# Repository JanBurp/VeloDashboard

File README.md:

# Velo Dashboard

A bicycle computer made for velomobiles.

Walkthrough videos (dutch):
- https://www.youtube.com/watch?v=hqzajXb8Hd0 (inside velomobile)
- https://www.youtube.com/watch?v=B8IcSTC7h3M (test setup)

## Reasons

In the summer of 2022 i bought a second hand [Quest](https://www.velomobiel.nl/quest/) velomobile.
It was in very good shape, had only driven 8000km while only 10 years old, and it fits my budget.

But it was missing blinkers, had a 6V system on board, and two headlights which could be turned on independent from eachother. Which results in my Quest looking cross-eyed :-(
That could be done better.

I also struggled finding the 'perfect' bicycle computer to keep track of at least my current speed, average speed, maximum speed, time, time of the trip, distance, and at least two seperate distance counters.
The most anoying things of these computers are the small screens, the not so ideal combination of functions, button combo's etc. And a GPS one took too long to recognise my location (possibly due to the carbon body).

I took some inspiration found online from other velonauts. Such as:
- [VeloPuter](https://veloputer.wordpress.com/about/)
- [Arduino in VM](https://quest.robbroek.nl/search/label/arduino)
- [Velomobiel Led strip verlichting](https://bickyenzijnfietsen.blogspot.com/2018/10/velomobiel-led-strip-verlichting.html)

## Features

This bicycle computer for a velomibile has these features:

Lighting:
- Drive the normal LED lights that are standard in most velombiles (rear light, brake light, fog light and blinkers if present)
- Drive the (double) head light(s) in several steps (off, dim, normal, beam)
- Drive LED strips on each side of the velomobile. For blinkers (with nice animation!), and normal light for visibility (front, rear and brake lights).

Knobs & Display:
- Big OLED display so i can see it easy.
- All controls are on the steering wheel (with a 3D printed console).
- Knobs for the blinkers, lights and switching through several pages on the display.

Speed & Distance:
- Current speed
- Current average speed
- Current maximum speed
- Distance of current trip
- Total distance of current day
- Distance of previous day
- Average and maximum speed of previous day
- Total distance of the velomobile in total
- Total distance of the velomobile while in my ownership
- At least three different tocal counters wich can be reset independent

Time:
- Current clock time
- Driving time of current trip (excluding stops for traffic lights etc)
- Total time of current trip (including these stops)
- Driving and total time of previous day

Others:
- Current Cadans speed
- Battery status
- Battery saving modes
- Automatic turn off after a set time (to spare battery)
- Option to set the total distance
- Option to set the clock time
- Option to set the wheel circumference
- Optionts to reset all extra counters

# Result

I have a working prototype since december 2022, with several improvements and new featuers since then.

# Manual

## Dashboard

- The yellow buttons are for activating the blinkers. Press and it turns on. Press again to turn off. Press the other and the first one stops and the new one starts. The LED's in front of the dashboard reflects the state of the blinkers.
- The white buttons are for controlling the head and rear lights. And also the lights of the LEDstrips. Press the upper button increases intensity. The lower button decreases intensity. These modes exists: OFF, DIMLIGHT, NORMAL LIGHT, BEAM, FOG.
- The red button on the upper right turns the headlights into BEAM mode while pressed.
- The red button in the middle is not part of the computer: it is it's own circuit and turns of the horn (in my case a Hornitt).
- The black button on the right is for controlling the display on the computer. Pressing cycles to several pages of the display (see below). Long press turns the computer and display into SETUP mode (see below).

## Display modes

Normal pages of the display (cycles through with the blank button):

### Homescreen:
- Speed (big in the center)
- Current distance (topleft)
- Current clock time (topright)
- Average speed (bottomleft)
- Maximun speed (bottomright)
- Cadans / RPM (bottomcenter)
- Icons for headlights and rearligt (middleleft)
- Icons for blinkers and breaklight (topmiddle)
- Icon for battery status (middleright)

### Screen 2 (today):
- Average speed
- Max speed
- Time elapsed while driving (excluding stops)
- Time elapsed from start of driving (including stops)

### Screen 3 (distances):
- Distance of current drive
- Distance of today
- Distance of previous driving day
- Distance of Trip 1

### Screen 3 (totals):
- Total distance of velomobile in my ownershop
- Total distance of velomobile
- Distance of Trip 2
- Distance of Trip 3

## Setup

A long press on the blank button switches to the setup screens. And pressing normal cycles to the setup screens. Long pressing again switches to normal screens. Of the screens there is some help of how to setup the several options.

These are the setup pages:

- Trip - for resetting Trip 1,2 and 3.
- Clock - for setting the time
- Tyre -  for setting the tyre (used for measuring speed and distances). You can select and ERTRO value or in mm.
- Bike - setting the total distance of the bike.

## Others

The computer keeps track of battery status. If the battery is becoming low it will decreases the brightness of the LEDstrips the battery icon on the display starts to blink.

If the battery is very low/almost dead, it will spare itself by turning everything off.

If you forgot to switch the computer off, if will auto power off after three minutes. The last 20 seconds will be shown in the display. If you press a button or start cycling again, the auto-power-off timer will stop.

## Hardware

### Teensy 4.0

The computer is based around a [Teensy 4.0](https://www.pjrc.com/store/teensy40.html). My first attempt was made with a Arduino nano, which is cheaper and uses less power. But i wanted a clock. And the combination of driving LED strips and having an OLED screen was impossible (as far as i know) with te Arduino. The Teensy 4.0 has multiple i2c (OLED) and interrupts. And it also has a build in RTC (Real Time Clock) with power options for a small coin battery to keep the state of the clock. The Teensy has also lots of room for improvements or future additions (SD card storage for example).

### IP67 LEDstrips WS2812B

IP67 means rainproof. And WS2812B means it just has three wires to connect (5V, GND & Data). I have two of them, one for each side of the velomobile. But the computer can also run four of them in case you want four small ones instead of two large ones. I choose the large ones because of easier assembling on my Quest. Downside is it user more power.
Here is a guide for using [WS2812B LEDstrips](https://randomnerdtutorials.com/guide-for-ws2812b-addressable-rgb-led-strip-with-arduino/)

### Power

- For power i choose Lipo batteries of 12.6 Volts. Other batteries are possible.
- [Polo Mini Pushbutton Power Switch](https://www.pololu.com/product/2809) is a on/off switch, whith reverse protection and more.
- Power regulator to 5V. The Teensy has it's own regulator for 5V to 3.3V.

### LED drivers

For driving the front, rear, brake (and maybe blinker) LED's i use [Meanwell LDD Led drivers](https://www.meanwell.com/webapp/product/search.aspx?prod=LDD-L) (LDD-700 for now).

## Schematics

The raw schematics can be found in the [kicad folder](./kicad)

## Software

For developing i used [VScode](https://code.visualstudio.com/) with [PlatformIO](https://platformio.org/). Once setup, i found this much easier for developling compared the Arduino IDE. But thats a software developer speaking ;-)

## 3D print

A STL file for 3D printing the console can be found in the [3D folder](./3d).

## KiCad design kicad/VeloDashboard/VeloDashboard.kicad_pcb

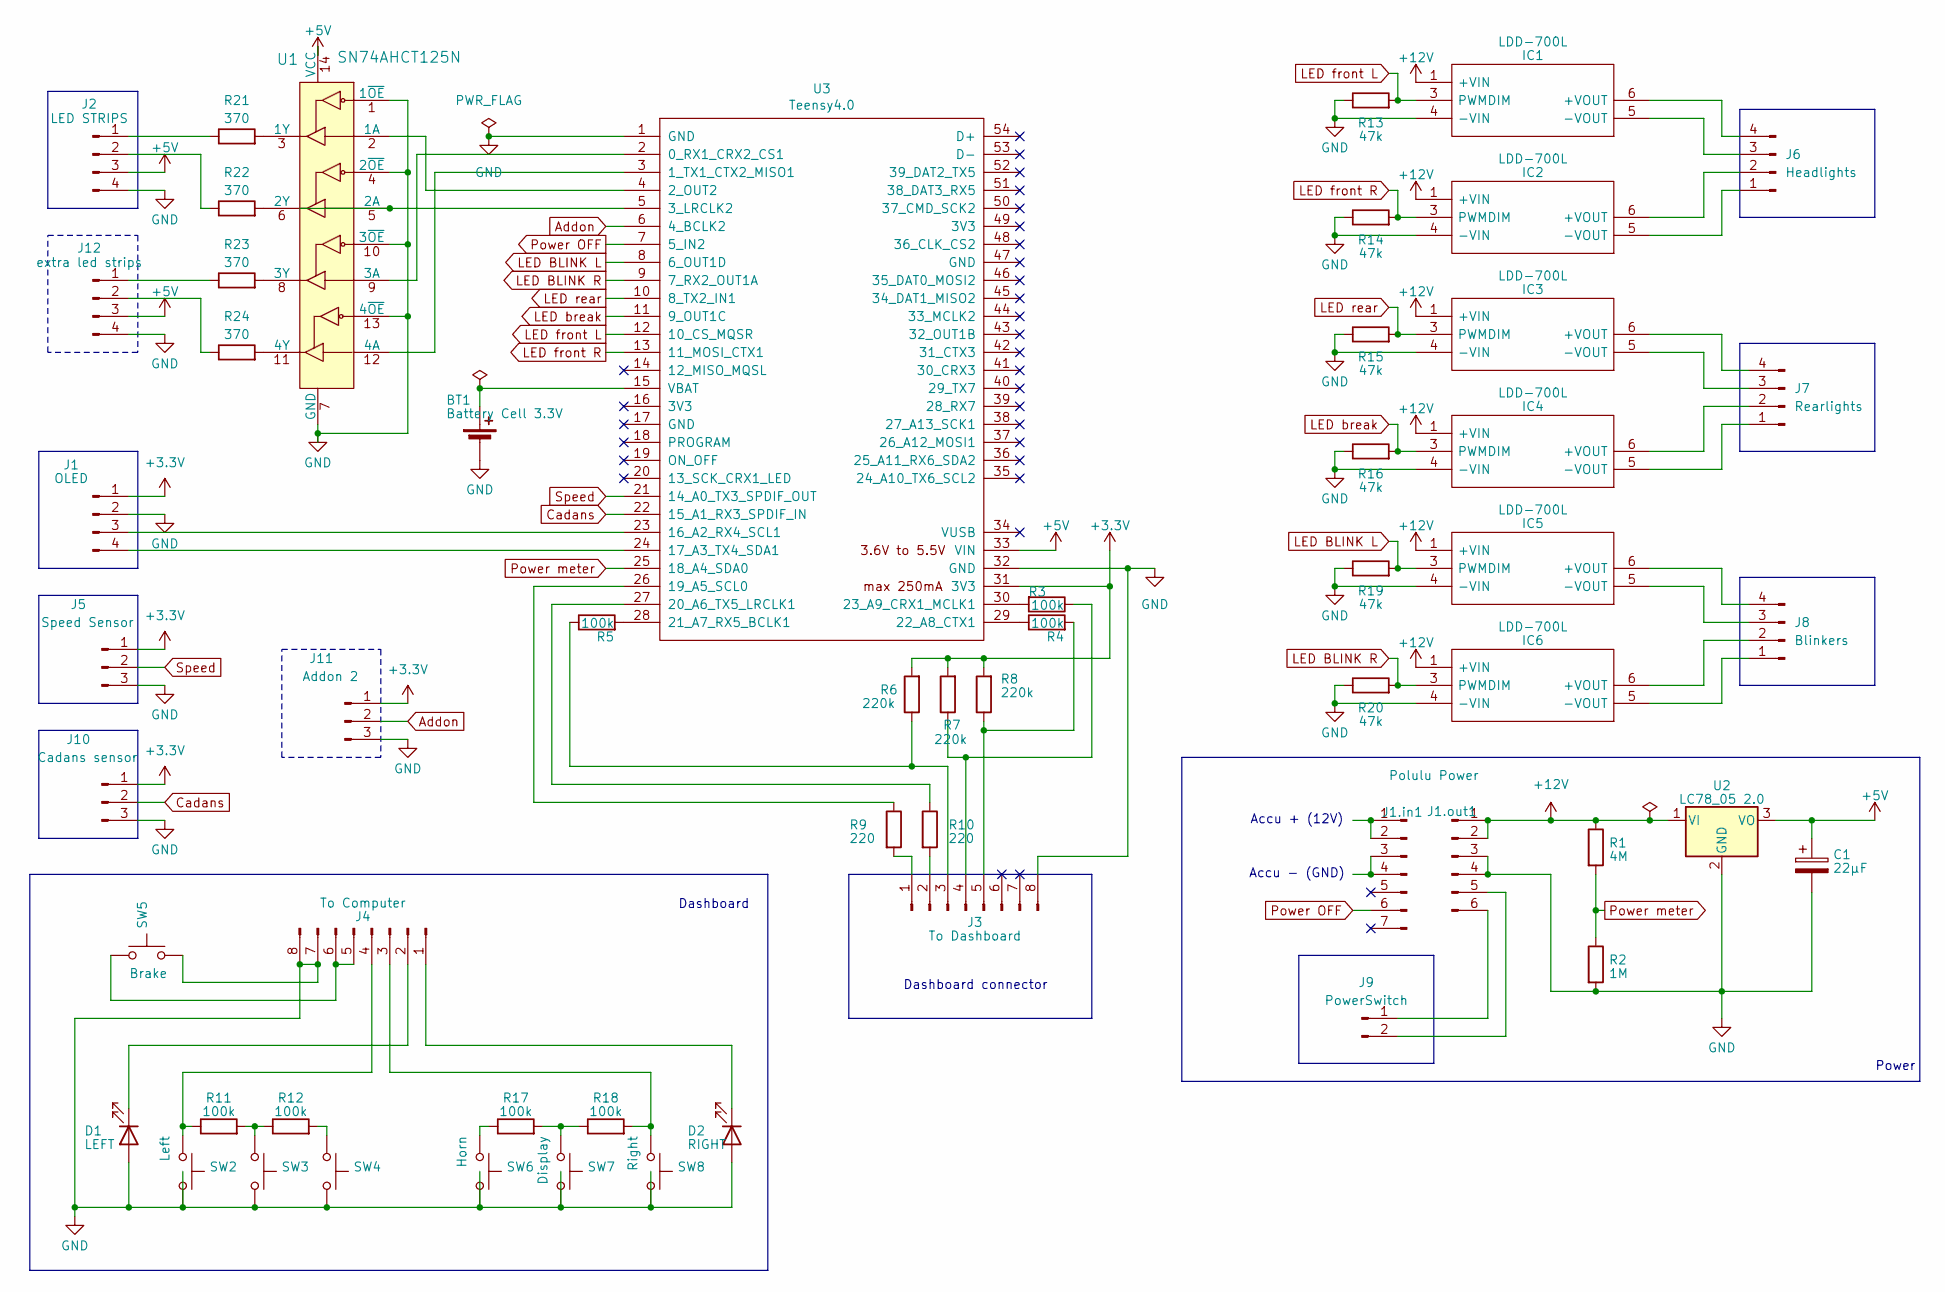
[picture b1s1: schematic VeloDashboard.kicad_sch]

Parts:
BT1: Battery Cell 3.3V; Battery_Panasonic_CR2032-HFN_Horizontal_CircularHoles
C1: 22µF; CP_Radial_D10.0mm_P7.50mm
D1: LEFT; LED_D5.0mm_Clear
D2: RIGHT; LED_D5.0mm_Clear
IC1, IC2, IC3, IC4, IC5, IC6: LDD-700L; LDD-XXXL; Mouser Part Number 709-LDD-700L
J1: OLED; PinHeader_1x04_P2.54mm_Horizontal
J1.in1: PinHeader_1x07_P2.54mm_Horizontal
J1.out1: Polulu Power; PinHeader_1x06_P2.54mm_Horizontal
J2: LED STRIPS; PinHeader_1x04_P2.54mm_Horizontal
J3: To Dashboard; PinHeader_1x08_P2.54mm_Horizontal
J4: To Computer; PinHeader_1x08_P2.54mm_Horizontal
J5: Speed Sensor; PinHeader_1x03_P2.54mm_Horizontal
J6: Headlights; PinHeader_1x04_P2.54mm_Horizontal
J7: Rearlights; PinHeader_1x04_P2.54mm_Horizontal
J8: Blinkers; PinHeader_1x04_P2.54mm_Horizontal
J9: PowerSwitch; PinHeader_1x02_P2.54mm_Horizontal
J10: Cadans sensor; PinHeader_1x03_P2.54mm_Horizontal
J11: Addon 2; PinHeader_1x03_P2.54mm_Horizontal
J12: extra led strips; PinHeader_1x04_P2.54mm_Horizontal
R1: 4M; R_Axial_DIN0207_L6.3mm_D2.5mm_P10.16mm_Horizontal
R2: 1M; R_Axial_DIN0207_L6.3mm_D2.5mm_P10.16mm_Horizontal
R3, R4, R5, R11, R12, R17, R18: 100k; R_Axial_DIN0207_L6.3mm_D2.5mm_P10.16mm_Horizontal
R6, R7, R8: 220k; R_Axial_DIN0207_L6.3mm_D2.5mm_P10.16mm_Horizontal
R9, R10: 220; R_Axial_DIN0207_L6.3mm_D2.5mm_P10.16mm_Horizontal
R13, R14, R15, R16, R19, R20: 47k; R_Axial_DIN0207_L6.3mm_D2.5mm_P10.16mm_Horizontal
R21, R22, R23, R24: 370; R_Axial_DIN0207_L6.3mm_D2.5mm_P10.16mm_Horizontal
SW2: Left; SW_PUSH-12mm
SW3: Down (lights); SW_PUSH-12mm
SW4: Up (lights); SW_PUSH-12mm
SW5: Brake; SW_PUSH-12mm
SW6: Horn; SW_PUSH-12mm
SW7: Display; SW_PUSH-12mm
SW8: Right; SW_PUSH-12mm
U1: SN74AHCT125N; DIP-14_W7.62mm_Socket_LongPads; MPN SN74AHCT125N; Digi-Key_PN 296-4655-5-ND
U2: LC78_05 2.0; TO-220-3_Vertical
U3: Teensy4.0; Teensy40_SMT

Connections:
+3.3V: J1.1, J5.1, J10.1, J11.1, R6.2, R7.2, R8.2, U3.31 (3V3)
+5V: C1.1, J2.3, J12.3, U1.14 (VCC), U2.3 (VO), U3.33 (VIN)
+12V: IC1.1 (+VIN), IC2.1 (+VIN), IC3.1 (+VIN), IC4.1 (+VIN), IC5.1 (+VIN), IC6.1 (+VIN), J1.out1.1, J1.out1.2, R1.1, U2.1 (VI)
Addon: J11.2, U3.6 (4_BCLK2)
Cadans: J10.2, U3.22 (15_A1_RX3_SPDIF_IN)
GND: BT1.2 (-), C1.2, D1.2 (A), D2.2 (A), IC1.4 (-VIN), IC2.4 (-VIN), IC3.4 (-VIN), IC4.4 (-VIN), IC5.4 (-VIN), IC6.4 (-VIN), J1.2, J1.out1.3, J1.out1.4, J2.4, J3.8, J4.7, J4.8, J5.3, J10.3, J11.3, J12.4, R2.2, R13.1, R14.1, R15.1, R16.1, R19.1, R20.1, SW2.2, SW3.2, SW4.2, SW5.2, SW6.2, SW7.2, SW8.2, U1.1 (1~OE), U1.4 (2~OE), U1.7 (GND), U1.10 (3~OE), U1.13 (4~OE), U2.2 (GND), U3.1 (GND), U3.32 (GND)
LED BLINK L: IC5.3 (PWMDIM), R19.2, U3.8 (6_OUT1D)
LED BLINK R: IC6.3 (PWMDIM), R20.2, U3.9 (7_RX2_OUT1A)
LED break: IC4.3 (PWMDIM), R16.2, U3.11 (9_OUT1C)
LED front L: IC1.3 (PWMDIM), R13.2, U3.12 (10_CS_MQSR)
LED front R: IC2.3 (PWMDIM), R14.2, U3.13 (11_MOSI_CTX1)
LED rear: IC3.3 (PWMDIM), R15.2, U3.10 (8_TX2_IN1)
unnamed: BT1.1 (+), U3.15 (VBAT)
unnamed: D1.1 (K), J4.2
unnamed: D2.1 (K), J4.1
unnamed: IC1.6 (+VOUT), J6.4
unnamed: IC1.5 (-VOUT), J6.3
unnamed: IC2.6 (+VOUT), J6.2
unnamed: IC2.5 (-VOUT), J6.1
unnamed: IC3.6 (+VOUT), J7.4
unnamed: IC3.5 (-VOUT), J7.3
unnamed: IC4.6 (+VOUT), J7.2
unnamed: IC4.5 (-VOUT), J7.1
unnamed: IC5.6 (+VOUT), J8.4
unnamed: IC5.5 (-VOUT), J8.3
unnamed: IC6.6 (+VOUT), J8.2
unnamed: IC6.5 (-VOUT), J8.1
unnamed: J1.3, U3.23 (16_A2_RX4_SCL1)
unnamed: J1.4, U3.24 (17_A3_TX4_SDA1)
unnamed: J1.in1.1, J1.in1.2
unnamed: J1.in1.3, J1.in1.4
unnamed: J1.out1.5, J9.2
unnamed: J1.out1.6, J9.1
unnamed: J2.1, R21.1
unnamed: J2.2, R22.1
unnamed: J3.1, R9.2
unnamed: J3.2, R10.2
unnamed: J3.3, R5.1, R6.1
unnamed: J3.4, R3.1, R7.1
unnamed: J3.5, R4.2, R8.1
unnamed: J4.3, R18.2, SW8.1
unnamed: J4.4, R11.1, SW2.1
unnamed: J4.5, J4.6, SW5.1
unnamed: J12.1, R23.1
unnamed: J12.2, R24.1
unnamed: R11.2, R12.1, SW3.1
unnamed: R12.2, SW4.1
unnamed: R17.1, SW6.1
unnamed: R17.2, R18.1, SW7.1
unnamed: U1.2 (1A), U3.4 (2_OUT2)
unnamed: R21.2, U1.3 (1Y)
unnamed: U1.5 (2A), U3.5 (3_LRCLK2)
unnamed: R22.2, U1.6 (2Y)
unnamed: U1.9 (3A), U3.2 (0_RX1_CRX2_CS1)
unnamed: R23.2, U1.8 (3Y)
unnamed: U1.12 (4A), U3.3 (1_TX1_CTX2_MISO1)
unnamed: R24.2, U1.11 (4Y)
unnamed: R9.1, U3.26 (19_A5_SCL0)
unnamed: R10.1, U3.27 (20_A6_TX5_LRCLK1)
unnamed: R5.2, U3.28 (21_A7_RX5_BCLK1)
unnamed: R4.1, U3.29 (22_A8_CTX1)
unnamed: R3.2, U3.30 (23_A9_CRX1_MCLK1)
Power OFF: J1.in1.6, U3.7 (5_IN2)
Power meter: R1.2, R2.1, U3.25 (18_A4_SDA0)
Speed: J5.2, U3.21 (14_A0_TX3_SPDIF_OUT)

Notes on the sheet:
Accu - (GND)
Dashboard
Power
Accu + (12V)
Dashboard connector

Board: 2 copper layers, 58 parts (0 on the bottom side), 65 nets, no tracks yet.

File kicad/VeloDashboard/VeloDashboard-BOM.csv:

"Reference","Value","Datasheet","Footprint","Qty","DNP"
"BT1","Battery Cell 3.3V","~","Battery:Battery_Panasonic_CR2032-HFN_Horizontal_CircularHoles","1",""
"C1","22µF","~","Capacitor_THT:CP_Radial_D10.0mm_P7.50mm","1",""
"D1","LEFT","~","LED_THT:LED_D5.0mm_Clear","1",""
"D2","RIGHT","~","LED_THT:LED_D5.0mm_Clear","1",""
"IC1,IC2,IC3,IC4,IC5,IC6","LDD-700L","https://datasheet.datasheetarchive.com/originals/distributor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","LDD:LDD-XXXL","6",""
"J1","OLED","~","Connector_PinHeader_2.54mm:PinHeader_1x04_P2.54mm_Horizontal","1",""
"J1.in1","~","~","Connector_PinHeader_2.54mm:PinHeader_1x07_P2.54mm_Horizontal","1",""
"J1.out1","Polulu Power","~","Connector_PinHeader_2.54mm:PinHeader_1x06_P2.54mm_Horizontal","1",""
"J2","LED STRIPS","~","Connector_PinHeader_2.54mm:PinHeader_1x04_P2.54mm_Horizontal","1",""
"J3","To Dashboard","~","Connector_PinHeader_2.54mm:PinHeader_1x08_P2.54mm_Horizontal","1",""
"J4","To Computer","~","Connector_PinHeader_2.54mm:PinHeader_1x08_P2.54mm_Horizontal","1",""
"J5","Speed Sensor","~","Connector_PinHeader_2.54mm:PinHeader_1x03_P2.54mm_Horizontal","1",""
"J6","Headlights","~","Connector_PinHeader_2.54mm:PinHeader_1x04_P2.54mm_Horizontal","1",""
"J7","Rearlights","~","Connector_PinHeader_2.54mm:PinHeader_1x04_P2.54mm_Horizontal","1",""
"J8","Blinkers","~","Connector_PinHeader_2.54mm:PinHeader_1x04_P2.54mm_Horizontal","1",""
"J9","PowerSwitch","~","Connector_PinHeader_2.54mm:PinHeader_1x02_P2.54mm_Horizontal","1",""
"J10","Addon 1","~","Connector_PinHeader_2.54mm:PinHeader_1x03_P2.54mm_Horizontal","1",""
"J11","Addon 2","~","Connector_PinHeader_2.54mm:PinHeader_1x03_P2.54mm_Horizontal","1",""
"J12","extra led strips","~","Connector_PinHeader_2.54mm:PinHeader_1x04_P2.54mm_Horizontal","1",""
"R1","4M","~","Resistor_THT:R_Axial_DIN0207_L6.3mm_D2.5mm_P10.16mm_Horizontal","1",""
"R2","1M","~","Resistor_THT:R_Axial_DIN0207_L6.3mm_D2.5mm_P10.16mm_Horizontal","1",""
"R3,R4,R5,R11,R12,R17,R18","100k","~","Resistor_THT:R_Axial_DIN0207_L6.3mm_D2.5mm_P10.16mm_Horizontal","7",""
"R6,R7,R8","220k","~","Resistor_THT:R_Axial_DIN0207_L6.3mm_D2.5mm_P10.16mm_Horizontal","3",""
"R9,R10","220","~","Resistor_THT:R_Axial_DIN0207_L6.3mm_D2.5mm_P10.16mm_Horizontal","2",""
"R13,R14,R15,R16,R19,R20","47k","~","Resistor_THT:R_Axial_DIN0207_L6.3mm_D2.5mm_P10.16mm_Horizontal","6",""
"R21,R22,R23,R24","370","~","Resistor_THT:R_Axial_DIN0207_L6.3mm_D2.5mm_P10.16mm_Horizontal","4",""
"SW2","Left","~","Button_Switch_THT:SW_PUSH-12mm","1",""
"SW3","Down (lights)","~","Button_Switch_THT:SW_PUSH-12mm","1",""
"SW4","Up (lights)","~","Button_Switch_THT:SW_PUSH-12mm","1",""
"SW5","Brake","~","Button_Switch_THT:SW_PUSH-12mm","1",""
"SW6","Horn","~","Button_Switch_THT:SW_PUSH-12mm","1",""
"SW7","Display","~","Button_Switch_THT:SW_PUSH-12mm","1",""
"SW8","Right","~","Button_Switch_THT:SW_PUSH-12mm","1",""
"U1","SN74AHCT125N","http://www.ti.com/general/docs/suppproductinfo.tsp?distId=10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","Package_DIP:DIP-14_W7.62mm_Socket_LongPads","1",""
"U2","LC78_05 2.0","https://www.onsemi.cn/PowerSolutions/document/MC7800-D.PDF","Package_TO_SOT_THT:TO-220-3_Vertical","1",""
"U3","Teensy4.0","","Teensy:Teensy40_SMT","1",""

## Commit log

2022-08-14 Working with simple LED’s
2022-08-14 Buzzer & Timings
2022-08-15 LEDstrips added
2022-08-16 Startup Animation
2022-08-16 Time adjustments
2022-08-20 Speed sensor & Display
2022-08-27 Speed stuff
2022-08-27 PlatformIO
2022-08-27 Speed Display
2022-08-27 Working on Teensy
2022-08-27 Refacturing Speed & Display
2022-08-27 LED strips working
2022-08-27 Small refacturing
2022-08-27 rewiring
2022-08-27 Clock added (not synced - maybe with GPS??)
2022-08-28 Display refacturing and pages
2022-08-28 Speed calculation refacturing
2022-08-28 Speed & Display finetuning
2022-08-29 Longer Ledstrip & color finetuning
2022-08-29 Speed finetuning
2022-09-20 No faster/slower indication
2022-09-20 Shorter welcome animation
2022-09-20 Nicer speed display
2022-09-20 dist & odo display
2022-09-20 Indicators in display
2022-09-20 Display finetuning
2022-09-21 Small bug
2022-09-21 Hardware pins changed (after soldering)
2022-09-21 Indicator switch (and UI button changed)
2022-09-21 RTC clock & battery
2022-09-21 ODO in EEPROM
2022-09-21 Display of time with flashing dots
2022-09-21 Extra button functions
2022-09-21 Small display change
2022-09-21 ODO finetuning
2022-09-21 Latest finetuning
2022-09-22 Finetune LEDS after installing
2022-09-23 debugging - analogRead
2022-09-23 Normal indicators
2022-09-23 bug: when changing indicators fast, no reset was done
2022-09-25 sensor analog read
2022-09-25 bug solved & use of trigger
2022-09-26 Speedometer refresh times
2022-09-26 Speedometer buffer changed
2022-09-26 Longer backlights
2022-09-26 TtipTime bug
2022-10-02 second flashing a bit faster
2022-10-02 set ODO
2022-10-02 simple power calculation
2022-10-02 Long blinkers
2022-10-02 Lights finetuning
2022-10-09 Disable unused pins
2022-10-09 Small adjustment to LED’s
2022-10-14 TEST number of LED’s and max current/brightness set
2022-10-14 TEST fake speed
2022-10-16 other timers (pt1)
2022-10-16 Smaller test setup
2022-10-16 Using Teensy Timers
2022-10-23 refacturing
2022-10-23 TEST is nicer implemented
2022-10-23 Wheels in settings
2022-10-23 battery indicator
2022-10-23 Icons for Battery & Lights - Knobs for Lights
2022-11-06 Control Dashboard (and some finetuning)
2022-11-13 LEDstrip usages indicator
2022-11-19 Battery Management
2022-11-20 Front (left) & Rear lights working
2022-11-20 contrast display
2022-11-21 cleanup
2022-11-21 finetuning battery
2022-11-25 PowerOff (after 60sec dead battery)
2022-12-03 Horn
2022-12-13 Hardware ready!
2022-12-24 5 buttons dahsboard
2022-12-27 Revert "Merge branch 'feature_3_battery' into develop"
    This reverts commit 6dc1b7cbc0be2a0b24a8220ec47080c7c38e3227, reversing
    changes made to c509d7db925ed054896ee03a1eab9e0b950f60f2.
2022-12-27 Battery Test
2022-12-27 Idle Timer & Pause Display
2023-01-02 New Dashboard
    - Better spread of buttons
    - No SHIFT button
    - Detection of LongPress
2023-01-03 Changes to Battery life measurement
2023-01-03 Display pages refactured
2023-01-06 test off (for bike)
2023-01-06 Display finetuning: no pause display
2023-01-06 UI: Indicator control: easy switch
2023-01-06 Display: Longpress (and other important changes) -> Homescreen
2023-01-08 Lights updated (front and rear with one function)
2023-01-08 Builtin LED off
2023-01-08 Teensy LED off (did not work)
2023-01-08 CPU speed to 24MHz
2023-01-08 normal CPU speed (needs another approach)
2023-01-08 Idle timer LEDstrips countdown animation
2023-01-08 Welcoms screen simpler
2023-01-08 Idle Timer warning shorter (30 secs)
2023-01-08 Display lower intensity when dark
2023-01-08 Indicator Animation
2023-01-08 Remove alarm function
2023-01-08 Adding lost km’s to ODO
2023-01-08 Some indicator animation bugs solved (timers…)
2023-01-08 Indicator Animation (almost there)
2023-01-13 Faster/Slower driehoekje niet laten zien bij stilstand
2023-01-13 Speed on other screens without digits
2023-01-13 typos
2023-01-13 test setup
2023-01-13 Indicator switch reageert nu meteen
2023-01-13 bug: als je meteen van de ene naar de andere richtingaanwijzer ging bleef strip zwart
2023-01-13 BEAM iets minder vel
2023-01-13 Changes to Dashboard & Display
    - FOG light only on after long press up
    - Lights off after long press down
    - Long press display -> nothing (will be MENU in future)
2023-01-13 Battery finetuning
2023-01-13 typo
2023-01-14 Display sensor only on HOME
2023-01-14 cleanup DEBUG
2023-01-14 More stuff in memory
2023-01-17 Bike settings & total
2023-02-05 Speed bugs (dayDist, tripTime, avg)
2023-02-05 bug: Speed not started
2023-02-05 test
2023-02-06 Better readable display pages
2023-02-06 Settings Menu (trip & total working)
2023-02-10 added more wheel circumferences (standards)
2023-02-13 Setting tyre circumference (some refacturing menu)
2023-02-17 first step for pcb
2023-02-17 bike = true
2023-02-24 Time shows hours:minutes when longer that an hour
2023-02-25 digital
2023-02-25 Teensy & LDD & Led strips
2023-02-27 Power & Dashboard & OLED & others
2023-03-06 buzzer with mosfet added
2023-04-09 pcb more
2023-04-09 Display deleted page prev avg/max
2023-04-09 bug: display settings should not be commented
2023-07-01 tighter dashboard buttons
2023-07-01 menu distribution
2023-07-01 develop
2023-07-01 Better Battery Measurement (due to horn)
2023-07-01 bug time display
2023-07-01 Remove contrast setting display
2023-07-01 Toeter & Relay toegevoegd
2023-07-01 Cleaner debug battery
2023-07-02 bike settings
2023-07-08 bug: on startup battery was dead
2023-07-09 bike
2023-07-16 After pause, ask if distance must be kept
2023-07-24 added 42-406
2023-07-24 Better power meter
2023-07-24 Set clock options
2023-07-24 Display more empt when count down
2023-07-24 Speed on top of menu
2023-07-24 busy with redesign display
2023-07-24 Less pages with nicer layout
2023-07-25 Nicer display layout
2023-07-25 swap time & distance
2023-07-25 Nederlands
2023-07-25 Last finetuning
2023-07-25 batery display finetuning
2023-07-25 swap clock & distance back
2023-07-25 bike setting
2023-08-08 Adjust battery level
2023-08-09 bug: When keeping day distance, time & avg where calculated wrong
2023-08-09 remove Horn / change to Beam
2023-08-27 Battery meter change
2023-09-02 Longer battery measurement
2023-09-02 Refacture speed
2023-09-02 remove old mem address
2023-09-02 size of slower/faster icon
2023-09-02 new Memory Struct (init & saved)
2023-09-03 new MemoryStruct
2023-09-04 Faster/Slower back to normal
2023-09-04 remove old MemStruct
2023-09-04 only ask startup if current distance > 100m
2023-09-04 Aks only when distance longer & brake is shor (within 6 hours)
2023-09-04 Avg calc better?
2023-09-04 Display for trip 2 & 3
2023-09-11 bug: current / day
2023-09-11 Teensy Clock speed
2023-09-12 slow cpu doesn’nt work
2023-09-12 Back to english
2023-09-12 48 Mhz CPU speed
2023-09-12 OLED less contrast
2023-09-12 CPU speed 80Mhz (48 gives LEDstrip problems)
2023-09-12 LEDstrips OFF (BLACK) when dimmed
2023-09-12 Shorter indicator LEDstrip Length
2023-09-16 Extra light setting
2023-09-16 bug in adding to totalDistance
2023-09-22 Lights finetuning (for power restrictions)
2023-09-22 finetune indicators
2023-09-22 speed indicator (start)
2023-10-05 BUG: startDay when should be resetCurrent
2023-10-05 swap speeds and today on display pages
2023-10-05 Flash faster/slower triangle
2023-10-05 Longer battery measurment
2023-10-25 turn off LEDstrip brake lights when paused
2023-10-29 Brakelight savind (off when paused)
2023-11-04 bug home screen
2023-11-17 no battery checking when brake is on - longer battery timing
2023-11-18 Battery Brake fineuning
2023-12-22 change ports (on test) to make easy room for UTP
2023-12-22 Indicartor LEDS on dashboard (utp)
2023-12-23 Dashboard working & no indicators on OLED
2023-12-23 Brake LED
2023-12-23 bug unused pins
2023-12-23 updatet schematics
2024-02-16 filter out strange doubling of (max)speed
2024-02-16 dimmed OLED on high beams
2024-02-16 dimmed > LIGHTS_ON
2024-02-16 dimmed is flickering to much…
2024-02-16 dimmed OLED
2024-02-16 cleanup code after dim
2024-02-16 moved to docs
2024-02-16 moved kicad project
2024-02-17 added 3d design
2024-07-12 pcb cleanup
2024-07-12 Added brakelights
2024-07-13 gitignore autosave
2024-07-13 dahsboard refacture
2024-07-13 Battery button same R
2024-07-13 Refacture schema
2024-07-13 update pcb
2024-07-13 added blinker drivers
2024-07-14 gitignore
2024-07-14 update to kicad 8
2024-07-14 footprints
2024-07-14 raw pcb
2024-07-14 rule check
2024-07-15 Refacture schematic & raw pcb
2024-07-15 Refacture voor uitbreidingen
2024-07-15 BOM added
2024-07-15 rewire dashboard connectors
2024-07-17 refacture due to soldering
2024-07-23 power adjustments
2024-07-23 New pins in code
2024-07-23 Buttons shuffle
2024-07-23 New code
2024-07-24 update dasbboard connector on computer
2024-07-24 Teensy internal LED on
2024-07-25 BUG: dashboard buttons threshold
2024-07-25 BUG: totaltime counted wrong
2024-07-25 hack to make high resistors work
2024-07-25 debug off
2024-07-25 TEST message & faster blinkers
2024-07-25 Don’t ask distance when TEST
2024-07-25 Speed indicator
2024-07-25 animation timing
2024-08-02 raw cadansSensor
2024-08-02 testing
2024-08-03 temp speed back to normal
2024-08-03 Indicatord back on display & shorter welcome
2024-08-03 Teensy internal LED off after power up animation
2024-08-04 added buzzer (hardware)
2024-08-04 busy buzzer
2024-08-04 buzzer working
2024-08-04 dashboard finetuning
2024-08-04 Keep distance question in monitor
2024-08-04 better test data
2024-08-04 first try
2024-08-04 second try
2024-08-04 third iteration
2024-08-04 allmost done!
2024-08-05 test on bike
2024-08-06 light indicators
2024-08-06 all has is place
2024-08-06 home display ready
2024-08-06 finetuning
2024-08-06 battery management: LEDstrips off when low
2024-08-06 prepare for animation rear lights
2024-08-06 in bike
2024-08-06 3D designs updated
2024-08-07 small display bugs
2024-08-07 bug: LEDstrips off when battery low
2024-08-07 font bug
2024-08-07 3D improvements
2024-08-07 added pictures & edited readme
2024-08-07 added 3D design pictures to text
2024-08-10 rearlight animation removed & dimming LEDstrips with lower battery
2024-08-10 bug: font for clock too big
2024-08-11 Bettery measurment, longer window
2024-08-11 develop mode off
2024-08-11 welcome screen
2024-08-11 new display pages
2024-08-16 bugs: calculating day totals & prev totals
2024-08-16 bug: vertical shift OLED
2024-08-16 speed calculations finetuning
2024-08-16 buzzer and timing
2024-08-17 smalle improvements & minor bugs
2025-09-21 better? speed filter
2025-09-21 achterLED standaard aan
2025-09-21 Remlichten na 5 seconden uit
2025-09-21 Kortere animatie
2025-09-21 Vraag naar continue, ook ok als rem aan staat.
2025-09-21 Minder voorLED’s aan
2025-09-21 Knipperlichten automatisch uit tijdens rijden (na 10s)
2025-09-21 minimal Display & bigger Indicators
2025-09-21 Timer for minimal display
2025-09-21 FIX: set clock
2025-09-26 minimal display a bit less minimal
2025-09-26 Longer auto-off indicators
2025-09-26 less filtereing of speed
2025-09-26 clang formmatter
2025-10-19 Better speedtrigger filtering?
2025-10-26 better speed detection?
2025-12-04 Minimal displaymode
2025-12-04 HOME display, next when fast, other to MINIMAL
2025-12-16 Adjust time pos on minimal display
